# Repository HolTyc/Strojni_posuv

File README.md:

# Strojni_posuv

This repo is about electric machine feed for machines like - milling cutter, lathe and more

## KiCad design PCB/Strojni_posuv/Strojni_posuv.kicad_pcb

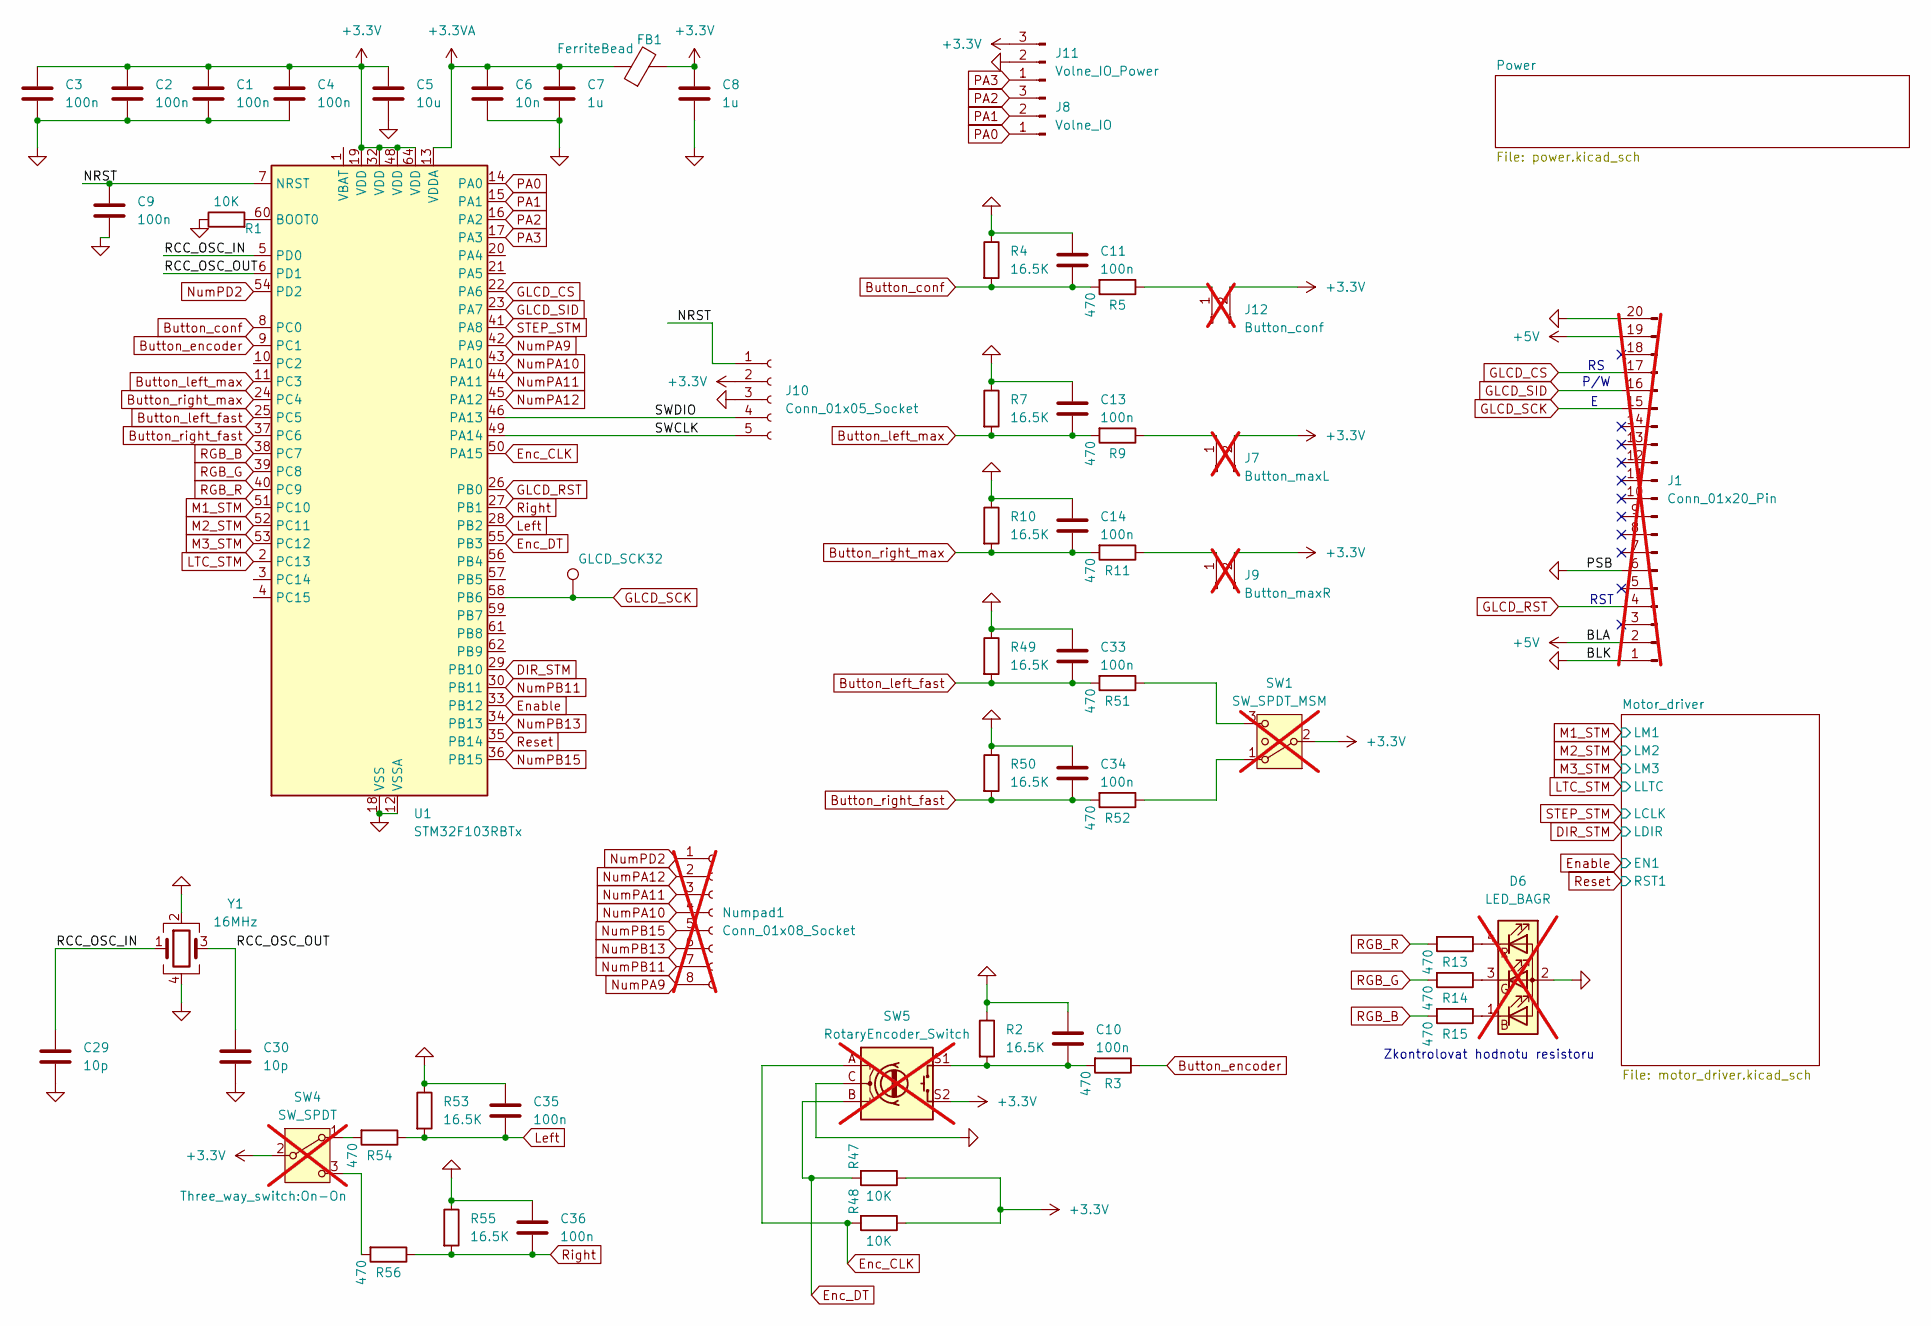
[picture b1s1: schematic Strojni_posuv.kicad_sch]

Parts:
C1, C2, C3, C4, C9, C10, C11, C13, C14, C33, C34, C35, C36: 100n; C_0603_1608Metric; LCSC C14663
C5: 10u; C_0603_1608Metric; LCSC C1691
C6: 10n; C_0603_1608Metric; LCSC C100042
C7, C8: 1u; C_0603_1608Metric; LCSC C15849
C29, C30: 10p; C_0603_1608Metric; LCSC C1634
D6: LED_BAGR; LED_D5.0mm-4_RGB_Wide_Pins; not fitted
FB1: FerriteBead; L_0603_1608Metric; LCSC C1002
GLCD_SCK32: TestPoint_Pad_D1.0mm
J1: Conn_01x20_Pin; PinSocket_1x20_P2.54mm_Vertical; not fitted
J7: Button_maxL; JST_XH_B2B-XH-A_1x02_P2.50mm_Vertical; not fitted
J8: Volne_IO; TerminalBlock_Xinya_XY308-2.54-3P_1x03_P2.54mm_Horizontal
J9: Button_maxR; JST_XH_B2B-XH-A_1x02_P2.50mm_Vertical; not fitted
J10: Conn_01x05_Socket; JST_PH_B5B-PH-K_1x05_P2.00mm_Vertical
J11: Volne_IO_Power; TerminalBlock_Xinya_XY308-2.54-3P_1x03_P2.54mm_Horizontal
J12: Button_conf; JST_XH_B2B-XH-A_1x02_P2.50mm_Vertical; not fitted
Numpad1: Conn_01x08_Socket; PinSocket_1x08_P2.54mm_Vertical; not fitted
R1, R47, R48: 10K; R_0805_2012Metric; LCSC C17414
R2, R4, R7, R10, R49, R50, R53, R55: 16.5K; R_0805_2012Metric; LCSC C2930171
R3, R5, R9, R11, R13, R14, R15, R51, R52, R54, R56: 470; R_0805_2012Metric; LCSC C17710
SW1: SW_SPDT_MSM; on_off_on; not fitted
SW4: SW_SPDT; On-On; not fitted
SW5: RotaryEncoder_Switch; Rotary_encoder_GME; not fitted
U1: STM32F103RBTx; LQFP-64_10x10mm_P0.5mm; LCSC C8735
Y1: 16MHz; Crystal_SMD_3225-4Pin_3.2x2.5mm; LCSC C112972

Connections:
+3.3V: C1.1, C2.1, C3.1, C4.1, C5.1, C8.1, FB1.2, J7.2, J9.2, J10.2, J11.3, J12.2, R47.1, R48.1, SW1.2 (3), SW4.2 (B), SW5.S2, U1.19 (VDD), U1.32 (VDD), U1.48 (VDD), U1.64 (VDD); also elsewhere on the board
+3.3VA: C6.1, C7.1, FB1.1, U1.13 (VDDA)
+5V: J1.2, J1.19; also elsewhere on the board
/NRST: C9.1, J10.1, U1.7 (NRST); also elsewhere on the board
/RCC_OSC_IN: C29.1, U1.5 (PD0), Y1.1
/RCC_OSC_OUT: C30.1, U1.6 (PD1), Y1.3
/SWCLK: J10.5, U1.49 (PA14); also elsewhere on the board
/SWDIO: J10.4, U1.46 (PA13); also elsewhere on the board
Button_conf: C11.2, R4.2, R5.2, U1.8 (PC0)
Button_encoder: R3.1, U1.9 (PC1)
Button_left_fast: C33.2, R49.2, R51.2, U1.25 (PC5)
Button_left_max: C13.2, R7.2, R9.2, U1.11 (PC3)
Button_right_fast: C34.2, R50.2, R52.2, U1.37 (PC6)
Button_right_max: C14.2, R10.2, R11.2, U1.24 (PC4)
DIR_STM: U1.29 (PB10); also elsewhere on the board
Enable: U1.33 (PB12); also elsewhere on the board
Enc_CLK: R48.2, SW5.A, U1.50 (PA15)
Enc_DT: R47.2, SW5.B, U1.55 (PB3)
GLCD_CS: J1.17, U1.22 (PA6)
GLCD_RST: J1.4, U1.26 (PB0)
GLCD_SCK: GLCD_SCK32.1, J1.15, U1.58 (PB6)
GLCD_SID: J1.16, U1.23 (PA7)
GND: C1.2, C2.2, C3.2, C4.2, C5.2, C6.2, C7.2, C8.2, C9.2, C10.1, C11.1, C13.1, C14.1, C29.2, C30.2, C33.1, C34.1, C35.1, C36.1, D6.2 (A), J1.1, J1.6, J1.20, J10.3, J11.2, R1.1, R2.1, R4.1, R7.1, R10.1, R49.1, R50.1, R53.1, R55.1, SW5.C, U1.12 (VSSA), U1.18 (VSS), U1.31 (VSS), U1.47 (VSS), U1.63 (VSS), Y1.2, Y1.4; also elsewhere on the board
LTC_STM: U1.2 (PC13); also elsewhere on the board
Left: C35.2, R53.2, R54.1, U1.28 (PB2)
M1_STM: U1.51 (PC10); also elsewhere on the board
M2_STM: U1.52 (PC11); also elsewhere on the board
M3_STM: U1.53 (PC12); also elsewhere on the board
unnamed: C10.2, R2.2, R3.2, SW5.S1
unnamed: D6.1 (BK), R15.1
unnamed: D6.3 (GK), R14.1
unnamed: D6.4 (RK), R13.1
unnamed: J7.1, R9.1
unnamed: J9.1, R11.1
unnamed: J12.1, R5.1
unnamed: R52.1, SW1.1
unnamed: R51.1, SW1.3 (4)
unnamed: R54.2, SW4.1 (A)
unnamed: R56.2, SW4.3 (C)
unnamed: R1.2, U1.60 (BOOT0)
NumPA9: Numpad1.8, U1.42 (PA9)
NumPA10: Numpad1.4, U1.43 (PA10)
NumPA11: Numpad1.3, U1.44 (PA11)
NumPA12: Numpad1.2, U1.45 (PA12)
NumPB11: Numpad1.7, U1.30 (PB11)
NumPB13: Numpad1.6, U1.34 (PB13)
NumPB15: Numpad1.5, U1.36 (PB15)
NumPD2: Numpad1.1, U1.54 (PD2)
PA0: J8.1, U1.14 (PA0)
PA1: J8.2, U1.15 (PA1)
PA2: J8.3, U1.16 (PA2)
PA3: J11.1, U1.17 (PA3)
RGB_B: R15.2, U1.38 (PC7)
RGB_G: R14.2, U1.39 (PC8)
RGB_R: R13.2, U1.40 (PC9)
Reset: U1.35 (PB14); also elsewhere on the board
Right: C36.2, R55.2, R56.1, U1.27 (PB1)
STEP_STM: U1.41 (PA8); also elsewhere on the board

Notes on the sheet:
P/W
RST
Zkontrolovat hodnotu resistoru

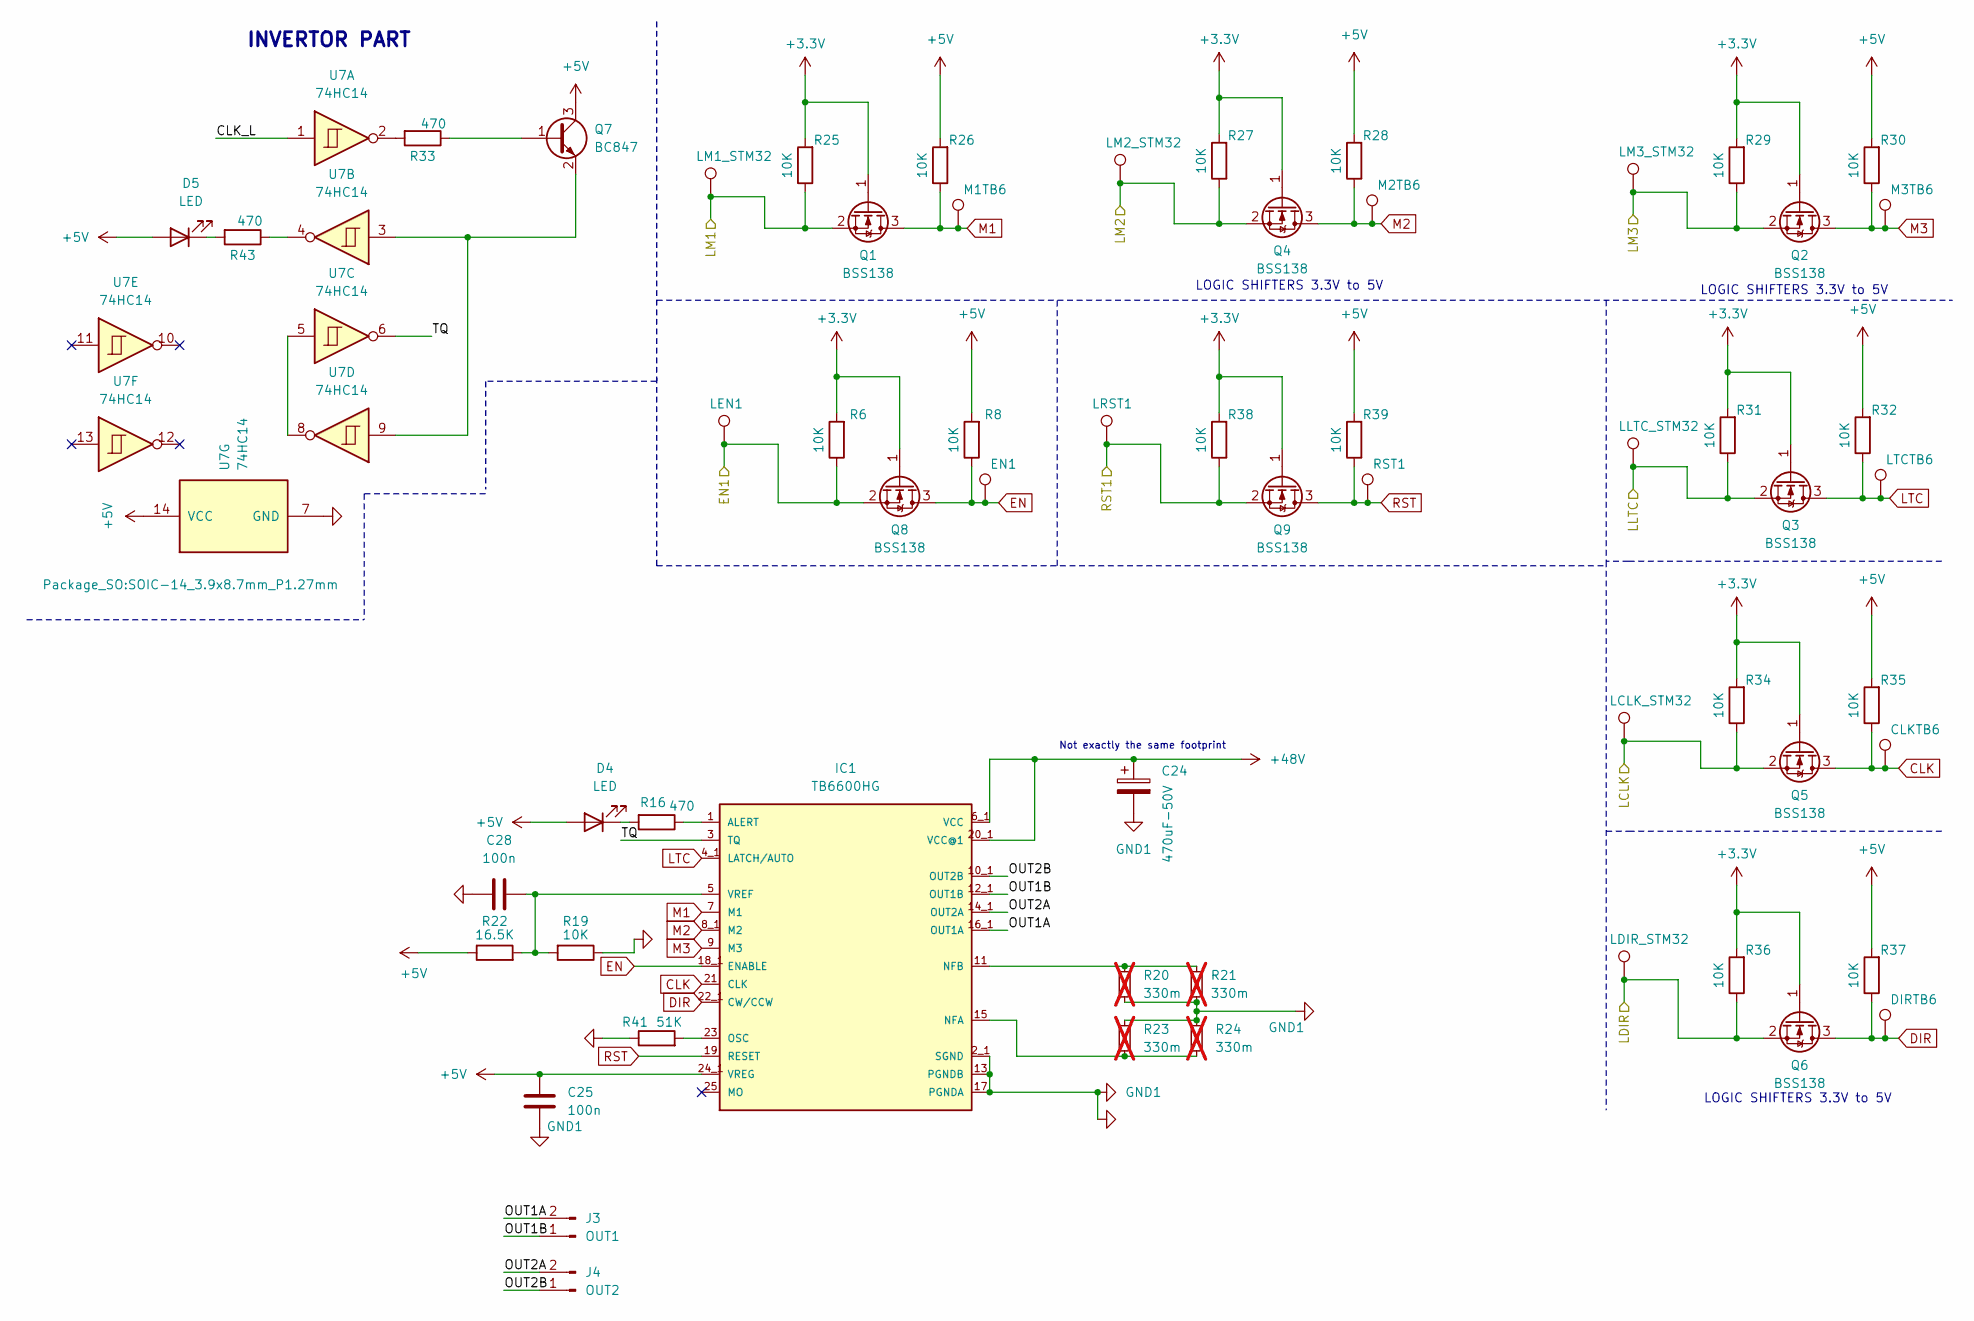
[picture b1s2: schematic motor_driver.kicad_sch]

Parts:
C24: 470uF-50V; CP_Elec_12.5x16; LCSC C249547
C25, C28: 100n; C_0603_1608Metric; LCSC C14663
CLKTB6: TestPoint_Pad_D1.0mm
D4, D5: LED; LED_0603_1608Metric; LCSC C84266
DIRTB6: TestPoint_Pad_D1.0mm
EN1: TestPoint_Pad_D1.0mm
IC1: TB6600HG; HZIP25-P-1.00F; LCSC C66042
J3: OUT1; TerminalBlock_Phoenix_MKDS-1,5-2-5.08_1x02_P5.08mm_Horizont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
J4: OUT2; TerminalBlock_Phoenix_MKDS-1,5-2-5.08_1x02_P5.08mm_Horizont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
LCLK_STM32: TestPoint_Pad_D1.0mm
LDIR_STM32: TestPoint_Pad_D1.0mm
LEN1: TestPoint_Pad_D1.0mm
LLTC_STM32: TestPoint_Pad_D1.0mm
LM1_STM32, LM2_STM32, LM3_STM32: TestPoint_Pad_D1.0mm
LRST1: TestPoint_Pad_D1.0mm
LTCTB6: TestPoint_Pad_D1.0mm
M1TB6, M2TB6, M3TB6: TestPoint_Pad_D1.0mm
Q1, Q2, Q3, Q4, Q5, Q6, Q8, Q9: BSS138; SOT-23; LCSC C78284
Q7: BC847; SOT-23; LCSC C8664
R6, R8, R19, R25, R26, R27, R28, R29, R30, R31, R32, R34, R35, R36, R37, R38, R39: 10K; R_0805_2012Metric; LCSC C17414
R16, R33, R43: 470; R_0805_2012Metric; LCSC C17710
R20, R21, R23, R24: 330m; R_Axial_DIN0922_L20.0mm_D9.0mm_P30.48mm_Horizontal; not fitted
R22: 16.5K; R_0805_2012Metric; LCSC C2930171
R41: 51K; R_0805_2012Metric; LCSC C17737
RST1: TestPoint_Pad_D1.0mm
U7: 74HC14; SOIC-14_3.9x8.7mm_P1.27mm; LCSC C5605

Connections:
+3.3V: Q1.1 (G), Q2.1 (G), Q3.1 (G), Q4.1 (G), Q5.1 (G), Q6.1 (G), Q8.1 (G), Q9.1 (G), R6.2, R25.2, R27.2, R29.2, R31.2, R34.2, R36.2, R38.2; also elsewhere on the board
+5V: C25.1, D4.2 (A), D5.2 (A), IC1.24_1 (VREG), Q7.3 (C), R8.2, R22.1, R26.2, R28.2, R30.2, R32.2, R35.2, R37.2, R39.2, U7.14 (VCC); also elsewhere on the board
+48V: C24.1, IC1.6_1 (VCC), IC1.20_1 (VCC@1); also elsewhere on the board
/Motor_driver/CLK_L: U7.1
/Motor_driver/OUT1A: IC1.16_1 (OUT1A), J3.2
/Motor_driver/OUT1B: IC1.12_1 (OUT1B), J3.1
/Motor_driver/OUT2A: IC1.14_1 (OUT2A), J4.2
/Motor_driver/OUT2B: IC1.10_1 (OUT2B), J4.1
/Motor_driver/TQ: IC1.3 (TQ), U7.6
CLK: CLKTB6.1, IC1.21 (CLK), Q5.3 (D), R35.1
DIR: DIRTB6.1, IC1.22_1 (CW/CCW), Q6.3 (D), R37.1
DIR_STM: LDIR_STM32.1, Q6.2 (S), R36.1; also elsewhere on the board
EN: EN1.1, IC1.18_1 (ENABLE), Q8.3 (D), R8.1
Enable: LEN1.1, Q8.2 (S), R6.1; also elsewhere on the board
GND: C24.2, C25.2, C28.1, IC1.2_1 (SGND), IC1.13 (PGNDB), IC1.17 (PGNDA), R19.1, R20.2, R21.2, R23.1, R24.1, R41.1, U7.7 (GND); also elsewhere on the board
LTC: IC1.4_1 (LATCH/AUTO), LTCTB6.1, Q3.3 (D), R32.1
LTC_STM: LLTC_STM32.1, Q3.2 (S), R31.1; also elsewhere on the board
M1: IC1.7 (M1), M1TB6.1, Q1.3 (D), R26.1
M1_STM: LM1_STM32.1, Q1.2 (S), R25.1; also elsewhere on the board
M2: IC1.8_1 (M2), M2TB6.1, Q4.3 (D), R28.1
M2_STM: LM2_STM32.1, Q4.2 (S), R27.1; also elsewhere on the board
M3: IC1.9 (M3), M3TB6.1, Q2.3 (D), R30.1
M3_STM: LM3_STM32.1, Q2.2 (S), R29.1; also elsewhere on the board
unnamed: D4.1 (K), R16.2
unnamed: D5.1 (K), R43.2
unnamed: IC1.1 (ALERT), R16.1
unnamed: IC1.15 (NFA), R23.2, R24.2
unnamed: IC1.11 (NFB), R20.1, R21.1
unnamed: IC1.23 (OSC), R41.2
unnamed: C28.2, IC1.5 (VREF), R19.2, R22.2
unnamed: Q7.1 (B), R33.1
unnamed: Q7.2 (E), U7.3, U7.9
unnamed: R33.2, U7.2
unnamed: R43.1, U7.4
unnamed: U7.5, U7.8
RST: IC1.19 (RESET), Q9.3 (D), R39.1, RST1.1
Reset: LRST1.1, Q9.2 (S), R38.1; also elsewhere on the board
STEP_STM: LCLK_STM32.1, Q5.2 (S), R34.1; also elsewhere on the board

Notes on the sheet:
LOGIC SHIFTERS 3.3V to 5V
INVERTOR PART
Not exactly the same footprint

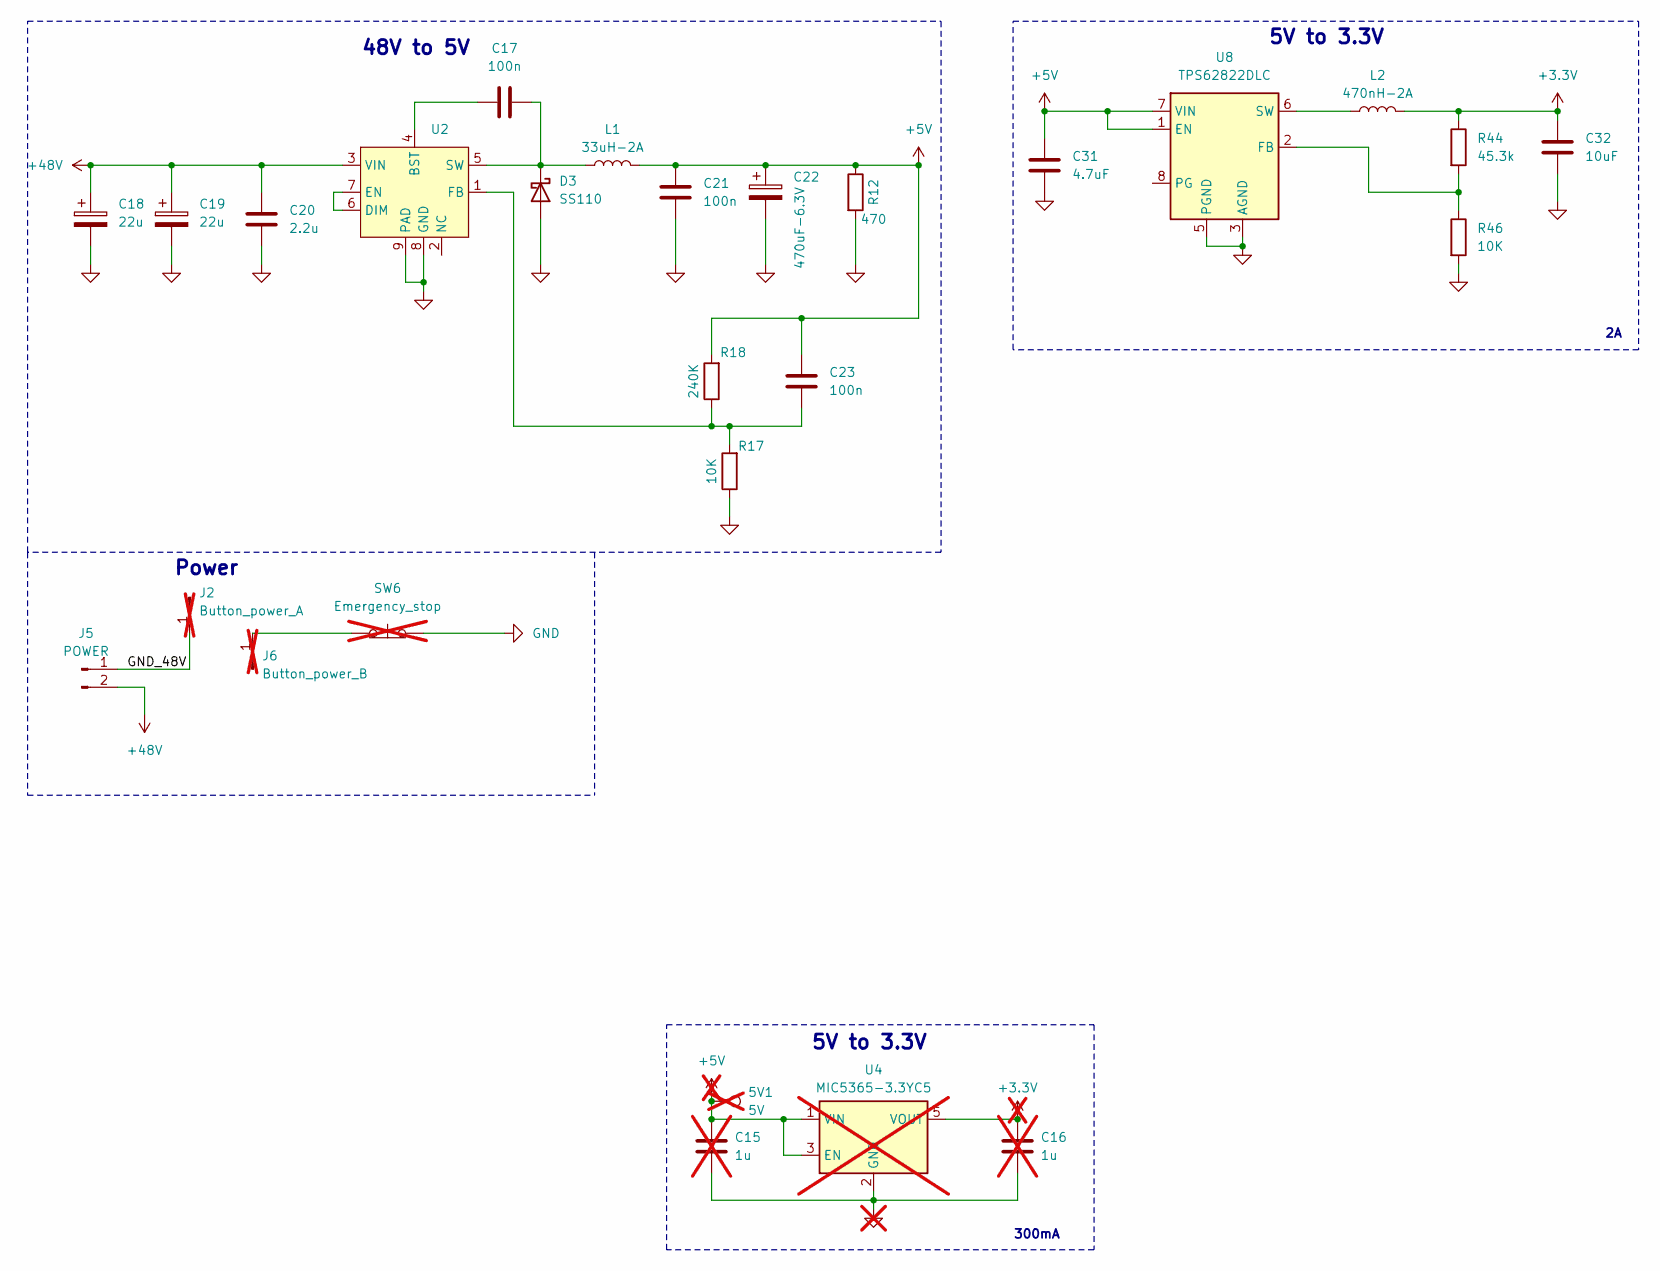
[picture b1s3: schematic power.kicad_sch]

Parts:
5V1: 5V; TestPoint_Pad_D1.5mm; not fitted
C15, C16: 1u; C_0603_1608Metric; LCSC C15849; not fitted
C17, C21, C23: 100n; C_0603_1608Metric; LCSC C14663
C18, C19: 22u; CP_Elec_6.3x5.4; LCSC C2836438
C20: 2.2u; C_0805_2012Metric; LCSC C513763
C22: 470uF-6.3V; CP_Elec_6.3x7.7; LCSC C114446
C31: 4.7uF; C_0805_2012Metric; LCSC C1779
C32: 10uF; C_0603_1608Metric; LCSC C19702
D3: SS110; D_SMA; LCSC C2482
J2: Button_power_A; Pin_D1.3mm_L11.3mm_W2.8mm_Flat; not fitted
J5: POWER; AMASS_XT60-M_1x02_P7.20mm_Vertical
J6: Button_power_B; Pin_D1.3mm_L11.3mm_W2.8mm_Flat; not fitted
L1: 33uH-2A; L_Sunlord_MWSA0603S; LCSC C408454
L2: 470nH-2A; L_1008_2520Metric; LCSC C964119
R12: 470; R_0805_2012Metric; LCSC C17710
R17, R46: 10K; R_0805_2012Metric; LCSC C17414
R18: 240K; R_0805_2012Metric; LCSC C25824
R44: 45.3k; R_0805_2012Metric; LCSC C322483
SW6: Emergency_stop; not fitted
U2: SOIC-8-1EP_3.9x4.9mm_P1.27mm_EP2.29x3mm; LCSC C404013
U4: MIC5365-3.3YC5; SOT-353_SC-70-5; LCSC C3021118; not fitted
U8: TPS62822DLC; Texas_VSON-HR-8_1.5x2mm_P0.5mm; LCSC C473385

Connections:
+3.3V: C16.2, C32.1, L2.2, R44.1, U4.5 (VOUT); also elsewhere on the board
+5V: 5V1.1, C15.2, C21.1, C22.1, C23.1, C31.1, L1.2, R12.1, R18.2, U4.1 (VIN), U4.3 (EN), U8.1 (EN), U8.7 (VIN); also elsewhere on the board
+48V: C18.1, C19.1, C20.1, J5.2, U2.3 (VIN); also elsewhere on the board
/Power/GND_48V: J2.1, J5.1
GND: C15.1, C16.1, C18.2, C19.2, C20.2, C21.2, C22.2, C31.2, C32.2, D3.2 (A), R12.2, R17.1, R46.2, SW6.2 (B), U2.8 (GND), U2.9 (PAD), U4.2 (GND), U8.3 (AGND), U8.5 (PGND); also elsewhere on the board
unnamed: C17.2, D3.1 (K), L1.1, U2.5 (SW)
unnamed: J6.1, SW6.1 (A)
unnamed: C17.1, U2.4 (BST)
unnamed: U2.6 (DIM), U2.7 (EN)
unnamed: C23.2, R17.2, R18.1, U2.1 (FB)
unnamed: R44.2, R46.1, U8.2 (FB)
unnamed: L2.1, U8.6 (SW)

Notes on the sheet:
48V to 5V
5V to 3.3V
300mA
Power

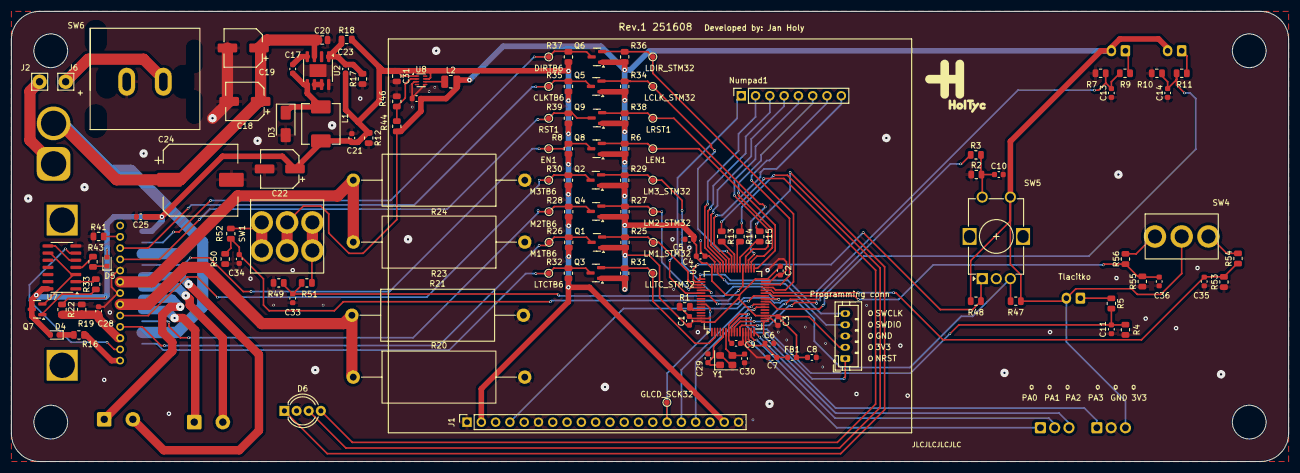
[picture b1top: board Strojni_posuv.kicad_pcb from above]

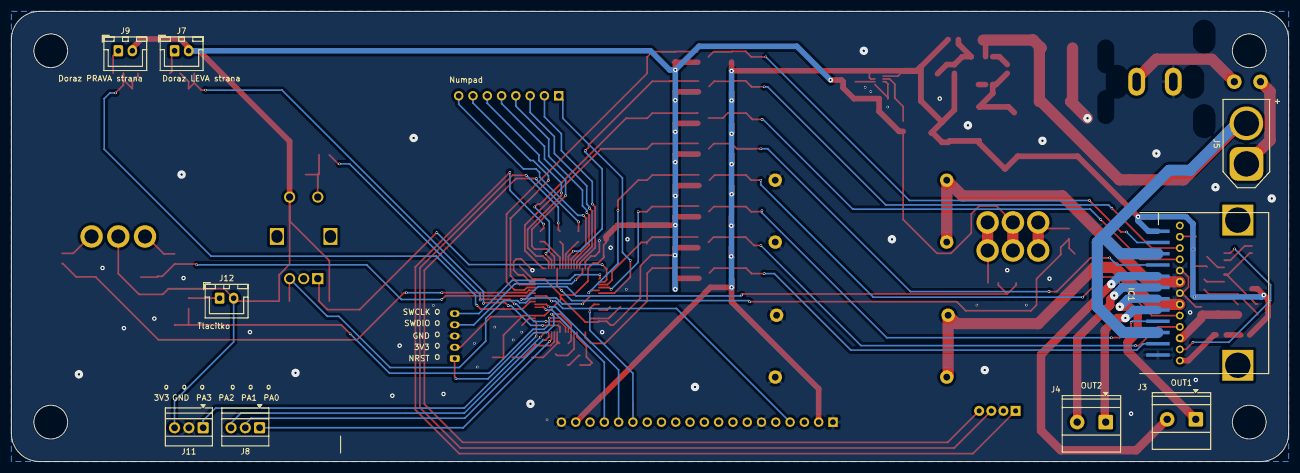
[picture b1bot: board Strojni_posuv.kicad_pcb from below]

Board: 2 copper layers, 227.0 x 80.0 mm, 140 parts (9 on the bottom side), 92 nets.

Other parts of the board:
Programming conn: Conn_01x05_Socket; JST_PH_B5B-PH-K_1x05_P2.00mm_Vertical

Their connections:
+3.3V: Programming conn.2; also elsewhere on the board
/NRST: Programming conn.1; also elsewhere on the board
/SWCLK: Programming conn.5; also elsewhere on the board
/SWDIO: Programming conn.4; also elsewhere on the board
GND: Programming conn.3; also elsewhere on the board

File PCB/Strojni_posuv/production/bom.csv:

Designator,Footprint,Quantity,Value,LCSC Part #
"C1, C10, C11, C13, C14, C17, C2, C21, C23, C25, C28, C3, C33, C34, C35, C36, C4, C9",0603,18,100n,C14663
"C18, C19",CP_Elec_6.3x5.4,2,22u,C2836438
C20,0805,1,2.2u,C513763
C22,CP_Elec_6.3x7.7,1,470uF-6.3V,C114446
C24,CP_Elec_12.5x16,1,470uF-50V,C249547
"C29, C30",0603,2,10p,C1634
C31,0805,1,4.7uF,C1779
C32,0603,1,10uF,C19702
C5,0603,1,10u,C1691
C6,0603,1,10n,C100042
"C7, C8",0603,2,1u,C15849
"CLKTB6, DIRTB6, EN1, GLCD_SCK32, LCLK_STM32, LDIR_STM32, LEN1, LLTC_STM32, LM1_STM32, LM2_STM32, LM3_STM32, LRST1, LTCTB6, M1TB6, M2TB6, M3TB6, RST1",TestPoint_Pad_D1.0mm,17,~,
D3,D_SMA,1,SS110,C2482
"D4, D5",0603,2,LED,C84266
FB1,0603,1,FerriteBead,C1002
IC1,HZIP25-P-1.00F,1,TB6600HG,C66042
J10,JST_PH_B5B-PH-K_1x05_P2.00mm_Vertical,1,Conn_01x05_Socket,
J11,TerminalBlock_Xinya_XY308-2.54-3P_1x03_P2.54mm_Horizontal,1,Volne_IO_Power,
J3,"TerminalBlock_Phoenix_MKDS-1,5-2-5.08_1x02_P5.08mm_Horizontal",1,OUT1,
J4,"TerminalBlock_Phoenix_MKDS-1,5-2-5.08_1x02_P5.08mm_Horizontal",1,OUT2,
J5,AMASS_XT60-M_1x02_P7.20mm_Vertical,1,POWER,
J8,TerminalBlock_Xinya_XY308-2.54-3P_1x03_P2.54mm_Horizontal,1,Volne_IO,
L1,L_Sunlord_MWSA0603S,1,33uH-2A,C408454
L2,1008,1,470nH-2A,C964119
"Q1, Q2, Q3, Q4, Q5, Q6, Q8, Q9",SOT-23,8,BSS138,C78284
Q7,SOT-23,1,BC847,C8664
"R1, R17, R19, R25, R26, R27, R28, R29, R30, R31, R32, R34, R35, R36, R37, R38, R39, R46, R47, R48, R6, R8",0805,22,10K,C17414
"R10, R2, R22, R4, R49, R50, R53, R55, R7",0805,9,16.5K,C2930171
"R11, R12, R13, R14, R15, R16, R3, R33, R43, R5, R51, R52, R54, R56, R9",0805,15,470,C17710
R18,0805,1,240K,C25824
R41,0805,1,51K,C17737
R44,0805,1,45.3k,C322483
U1,LQFP-64_10x10mm_P0.5mm,1,STM32F103RBTx,C8735
U2,SOIC-8-1EP_3.9x4.9mm_P1.27mm_EP2.29x3mm,1,~,C404013
U7,SOIC-14_3.9x8.7mm_P1.27mm,1,74HC14,C5605
U8,Texas_VSON-HR-8_1.5x2mm_P0.5mm,1,TPS62822DLC,C473385
Y1,Crystal_SMD_3225-4Pin_3.2x2.5mm,1,16MHz,C112972

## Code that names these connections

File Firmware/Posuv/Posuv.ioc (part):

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Mcu.Name=STM32F103R(8-B)Tx
Mcu.Package=LQFP64
Mcu.UserName=STM32F103RBTx
PA0-WKUP.Signal=ADCx_IN0
PA1.Signal=ADCx_IN1
PA10.GPIOParameters=GPIO_Label
PA10.GPIO_Label=Num_R4
PA10.Signal=GPIO_Output
PA11.GPIOParameters=GPIO_Label
PA11.GPIO_Label=Num_R3
PA11.Signal=GPIO_Output
PA12.GPIOParameters=GPIO_Label
PA12.GPIO_Label=Num_R2
PA12.Signal=GPIO_Output
PA13.Mode=Serial_Wire
PA13.Signal=SYS_JTMS-SWDIO
PA14.Mode=Serial_Wire
PA14.Signal=SYS_JTCK-SWCLK
PA15.GPIOParameters=GPIO_Label
PA15.GPIO_Label=ENC_CLK
PA15.Signal=S_TIM2_CH1_ETR
PA6.GPIOParameters=GPIO_Label
PA6.GPIO_Label=GLCD_CS
PA6.Signal=GPIO_Output
PA7.GPIOParameters=GPIO_Label
PA7.GPIO_Label=GLCD_SID
PA7.Signal=GPIO_Output
PA8.GPIOParameters=GPIO_Label
PA8.GPIO_Label=STEP
PA8.Signal=GPIO_Output
PA9.GPIOParameters=GPIO_Label
PA9.GPIO_Label=Num_C4
PA9.Signal=GPIO_Input
PB0.GPIOParameters=GPIO_Label
PB0.GPIO_Label=GLCD_RST
PB0.Signal=GPIO_Output
PB1.GPIOParameters=GPIO_Label
PB1.GPIO_Label=Right
PB1.Signal=GPIO_Input
PB10.GPIOParameters=GPIO_Label
PB10.GPIO_Label=DIR
PB10.Signal=GPIO_Output
PB11.GPIOParameters=GPIO_Label
PB11.GPIO_Label=Num_C3
PB11.Signal=GPIO_Input
PB12.GPIOParameters=GPIO_Label
PB12.GPIO_Label=Enable
PB12.Signal=GPIO_Output
PB13.GPIOParameters=GPIO_Label
PB13.GPIO_Label=Num_C2
PB13.Signal=GPIO_Input
PB14.GPIOParameters=GPIO_Label
PB14.GPIO_Label=Reset
PB14.Signal=GPIO_Output
PB15.GPIOParameters=GPIO_Label
PB15.GPIO_Label=Num_C1
PB15.Signal=GPIO_Input
PB2.GPIOParameters=GPIO_Label
PB2.GPIO_Label=Left
PB2.Signal=GPIO_Input
PB3.GPIOParameters=GPIO_Label
PB3.GPIO_Label=ENC_DT
PB3.Signal=S_TIM2_CH2
PB6.GPIOParameters=GPIO_Label
PB6.GPIO_Label=GLCD_SCK
PB6.Signal=GPIO_Output
PC0.GPIOParameters=GPIO_Label
PC0.GPIO_Label=Bconf
PC0.Signal=GPXTI0
PC1.GPIOParameters=GPIO_Label
PC1.GPIO_Label=Benc
PC1.Signal=GPXTI1
PC10.GPIOParameters=GPIO_Label
PC10.GPIO_Label=M1
PC10.Signal=GPIO_Output
PC11.GPIOParameters=GPIO_Label
PC11.GPIO_Label=M2
PC11.Signal=GPIO_Output
PC12.GPIOParameters=GPIO_Label
PC12.GPIO_Label=M3
PC12.Signal=GPIO_Output
PC13-TAMPER-RTC.GPIOParameters=GPIO_Label
PC13-TAMPER-RTC.GPIO_Label=LTC
PC13-TAMPER-RTC.Signal=GPIO_Output
PC3.GPIOParameters=GPIO_Label
PC3.GPIO_Label=Bleft_max
PC3.Signal=GPXTI3
PC4.GPIOParameters=GPIO_Label
PC4.GPIO_Label=Bright_max
PC4.Signal=GPXTI4
PC5.GPIOParameters=GPIO_Label
PC5.GPIO_Label=Bleft_fast
PC5.Signal=GPXTI5
PC6.GPIOParameters=GPIO_Label
PC6.GPIO_Label=Bright_fast
PC6.Signal=GPXTI6
PC7.GPIOParameters=GPIO_Label
PC7.GPIO_Label=RGB_G
PC7.Signal=GPIO_Output
PC8.GPIOParameters=GPIO_Label
PC8.GPIO_Label=RGB_B
PC8.Signal=GPIO_Output
PC9.GPIOParameters=GPIO_Label
PC9.GPIO_Label=RGB_R
PC9.Signal=GPIO_Output
PD0-OSC_IN.Mode=HSE-External-Oscillator
PD0-OSC_IN.Signal=RCC_OSC_IN
PD1-OSC_OUT.Mode=HSE-External-Oscillator
PD1-OSC_OUT.Signal=RCC_OSC_OUT
PD2.GPIOParameters=GPIO_Label
PD2.GPIO_Label=Num_R1
PD2.Signal=GPIO_Output
RCC.HSE_VALUE=16000000
RCC.SYSCLKFreq_VALUE=64000000
RCC.SYSCLKSource=RCC_SYSCLKSOURCE_PLLCLK
board=custom

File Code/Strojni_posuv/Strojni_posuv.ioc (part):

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Mcu.Name=STM32F103R(8-B)Tx
Mcu.Package=LQFP64
Mcu.UserName=STM32F103RBTx
PA0-WKUP.Signal=ADCx_IN0
PA1.Signal=ADCx_IN1
PA13.Mode=Serial_Wire
PA13.Signal=SYS_JTMS-SWDIO
PA14.Mode=Serial_Wire
PA14.Signal=SYS_JTCK-SWCLK
PA6.GPIOParameters=GPIO_Label
PA6.GPIO_Label=GLCD_CS
PA6.Signal=GPIO_Output
PA7.GPIOParameters=GPIO_Label
PA7.GPIO_Label=GLCD_SID
PA7.Signal=GPIO_Output
PA8.GPIOParameters=GPIO_Label
PA8.GPIO_Label=STEP
PA8.Signal=GPIO_Output
PB0.GPIOParameters=GPIO_Label
PB0.GPIO_Label=GLCD_RST
PB0.Signal=GPIO_Output
PB10.GPIOParameters=GPIO_Label
PB10.GPIO_Label=DIR
PB10.Signal=GPIO_Output
PB6.GPIOParameters=GPIO_Label
PB6.GPIO_Label=GLCD_SCK
PB6.Signal=GPIO_Output
PC0.GPIOParameters=GPIO_Label
PC0.GPIO_Label=Button_conf
PC0.Signal=GPXTI0
PC1.GPIOParameters=GPIO_Label
PC1.GPIO_Label=Button_prec
PC1.Signal=GPXTI1
PC2.GPIOParameters=GPIO_Label
PC2.GPIO_Label=Button_gen_stop
PC2.Signal=GPXTI2
PC3.GPIOParameters=GPIO_Label
PC3.GPIO_Label=Button_left_max
PC3.Signal=GPXTI3
PC4.GPIOParameters=GPIO_Label
PC4.GPIO_Label=Button_right_max
PC4.Signal=GPXTI4
PC7.GPIOParameters=GPIO_Label
PC7.GPIO_Label=RGB_B
PC7.Signal=GPIO_Output
PC8.GPIOParameters=GPIO_Label
PC8.GPIO_Label=RGB_G
PC8.Signal=GPIO_Output
PC9.GPIOParameters=GPIO_Label
PC9.GPIO_Label=RGB_R
PC9.Signal=GPIO_Output
PD0-OSC_IN.Mode=HSE-External-Oscillator
PD0-OSC_IN.Signal=RCC_OSC_IN
PD1-OSC_OUT.Mode=HSE-External-Oscillator
PD1-OSC_OUT.Signal=RCC_OSC_OUT
board=custom

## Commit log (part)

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2024-08-22 Init - I changed README.md with some dummy text
2024-08-22 Useful materials New useful links
2024-08-25 Starting with PCB Adding MCU and routing all buttons and power (on MCU)
2024-08-26 PCB making #1 Power management
2024-09-02 Learning, PCB making #2 Added new links to Learning Motor driver part in Kicad, Power part (48V to 5V), New pins to STM32F103
2024-09-07 PCB making #3 Whole motor driver, small power changes, STM32 clock and new pin configuration
2024-09-07 STM code #1 Created code folder and main init, Pin configuration
2024-09-08 PCB making #4 Finding components on JLCPCB and adding their tags to schematic. Assigning almost all footprints
2024-09-11 PCB making #5 Starting with component placement
2024-09-15 PCB making #6 Placing all components - component layout
2024-09-26 New materials + Schuzka
2025-02-07 New chapter of PCB making #1
    the grind continuesmkdir Useful_materials. redundant systems for 5V logic shifting. 2. rotary encoder. 3. new buttons. 4. placement of components (it is not completed)
2025-02-07 New chapter of PCB making #2
    pcb placement
2025-02-11 Revision 0
    The PCB is done
2025-02-13 Revision 0 - final
    I send this files to JLCPCB
2025-03-09 Components
    New motor
2025-05-04 Last version before making new revision
2025-05-06 Problems that I need to address and list of functions
2025-07-21 Starting new Revision 1
    addressing some problems and mistakes
2025-08-03 Resolving problems from list
2025-08-05 Schema done?
    I think that I have functional schema, but it needs a check
2025-08-07 PCB done?
    I did all the routing and component placement on PCB
2025-08-07 Small changes
    I needed to update the board to version 9.0 and relocate some silkscreen items
2025-08-15 Numpad + small changes
    I added numpad and add some description to components
2025-08-16 Revision 1 251608
    Production version
2025-12-07 Last version with Li-ion
